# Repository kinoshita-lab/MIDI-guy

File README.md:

# MIDI Guy by Kinoshita Laboratory

[japanese version](./README.ja.md)

MIDI Guy is a sound module with SAM2695, a single chip General MIDI(GM) synthesizer.
It can generate GM's 127 sound programs such as "Acoustic Grand Piano", "Trumpet", etc.

You can also use effects and EQs. Please refer to the SAM2695's datasheet for details.
<https://www.dream.fr/pdf/Serie2000/SAM_Datasheets/SAM2695.pdf>

# Selling PCBA at tindie.com!
Please visit: <https://www.tindie.com/products/kinoshitalab/midi-guy-rev-21-kit/>

## What's new for Revision 2.1

- USB Power input is replaced from micro USB to USB Type-C
- PCB Dimension modification: fit for Frisk case
- Support both TRS MIDI type A and B
- Add UART In terminal for the convinience using with microcontroller

## Kit contents

- Pre-assembled circuit board
- 2 pcs. of 3.5mm TRS Jack
- 1 pc. of DIN <-> TRS(Type A) Conversion Cable

## What you will need

- USB C Cable
- Power source for USB, such as power adapter or PC
- MIDI cable
- MIDI Output Device e.g. MIDI Keyboard, PC with MIDI Interface

## How to assemble

Solder the included TRS Jacks to the places shown below.

## Usage

- Power: Connect the power source from USB
- MIDI In: Connect a MIDI message source(e.g. MIDI Keyboard, MIDI Interface connected to a PC)
- Audio Out: Outputs stereo sound, you can connect headphones directly.

## Schematics, design data, questions

<https://github.com/kinoshita-lab/MIDI-guy>

## Case Design
STL file made by @maks. Thank you!!
https://www.printables.com/model/1151667-case-for-a-midi-guy-pcb

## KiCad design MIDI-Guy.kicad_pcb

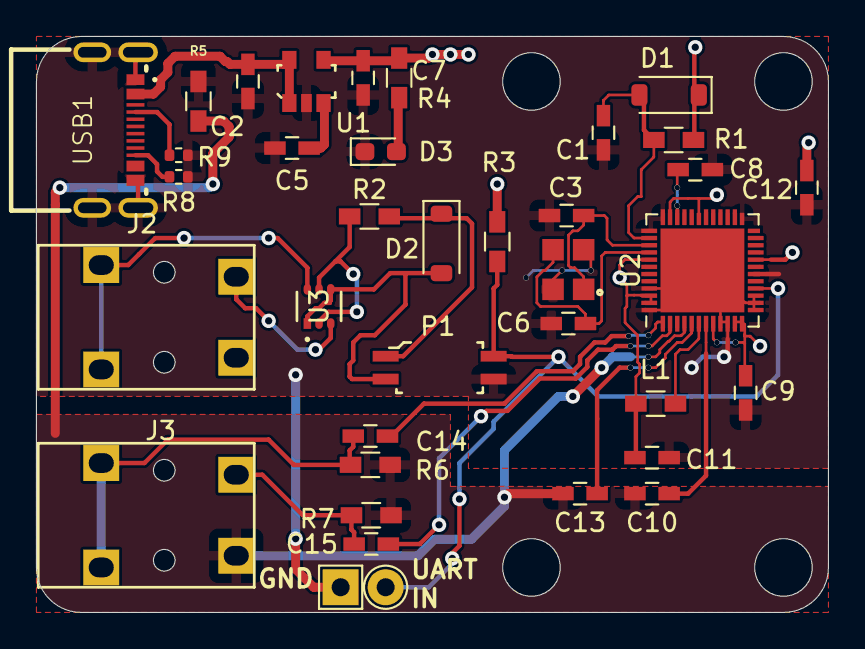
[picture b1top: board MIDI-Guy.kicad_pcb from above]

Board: 2 copper layers, 44.0 x 32.0 mm, 39 parts (0 on the bottom side), 25 nets.

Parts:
C1, C10: 1u; C_0603_HandSoldering
C2, C7, C14, C15: 10u; C_0603_HandSoldering
C3, C6: 10p; C_0603_HandSoldering
C5: 0.01u; C_0603_HandSoldering
C8: 4.7u; C_0603_HandSoldering
C9, C11, C12, C13: 0.1u; C_0603_HandSoldering
D1, D2: SM4007PL; D_SOD-123
D3: LED; LED_0603_1608Metric_Pad1.05x0.95mm_HandSolder
J2, J3: AudioJack3; 3.5mm_Stereo_TRS_PJ-3210-4A_and_ST-005-G
L1: GZ1608D222TF; L_0603_HandSoldering
P1: TLP291(GB-TP,SE; TLP291
R1: 10k; R_0603_HandSoldering
R2, R3: 220; R_0603_HandSoldering
R4: 1k; R_0603_HandSoldering
R5: 0; R_0603_HandSoldering
R6, R7: 47k; R_0603_HandSoldering
R8, R9: 5.1k; R_0402_1005Metric
REFe: MountingHole_3.2mm_M3_DIN965
REFe#2: MountingHole_3.2mm_M3_DIN965
TP1: TestPoint; TestPoint_THTPad_D2.0mm_Drill1.0mm
TP2: TestPoint; TestPoint_THTPad_2.0x2.0mm_Drill1.0mm
U1: TAR5S33; TAR5S33_Akizuki_Toshiba_SSOP5
U2: SAM2695; SAM2695_QFN-48-6x6mm_Pitch0.4mm
U3: BAS40DW-04-7-F; SOT-363_DIO
USB1: HRO TYPE-C-31-M-08A
Y1: TAXM12M4RDBCCT2T; OSCSC320X250X100N

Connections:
+3V3: C7.1, C9.1, C11.1, C12.1, D1.1 (K), L1.1, R1.1, R3.2, R4.1, U1.4 (Vout), U2.8 (VD33), U2.11 (VD33), U2.12 (WR/), U2.20 (VD33), U2.31 (VD33), U2.35 (VD33), U2.41 (VD33), U2.46 (VD33), U2.47 (XDIV)
A1: D2.2 (A), P1.2, U3.1 (A1), U3.4 (A2)
C1: R2.2, U3.2 (C1), U3.5 (C2)
GND: C1.2, C2.2, C3.2, C5.2, C6.2, C7.2, C8.2, C9.2, C11.2, C12.2, D3.1 (K), P1.3, R5.2, R8.1, R9.2, TP2.1, U1.2 (GND), U2.9 (GND), U2.10 (A0), U2.13 (GND), U2.14 (CS/), U2.15 (RD/), U2.18 (GND), U2.25 (GND), U2.36 (GND), U2.37 (TEST), U2.45 (GND), U2.48 (GND), U2.49 (die_pad), USB1.1 (GND), USB1.12 (GND), USB1.13 (SHIELD), Y1.2 (GND), Y1.4 (GND)
GNDA: C10.2, C13.1, J3.S, R5.1, R6.1, R7.1, U2.4 (AGND)
unnamed: C14.1, J3.T, R6.2
unnamed: C15.1, J3.R, R7.2
unnamed: C1.1, D1.2 (A), R1.2, U2.38 (RST/PD/)
unnamed: D2.1 (K), P1.1, R2.1
unnamed: D3.2 (A), R4.2
unnamed: C2.1, U1.1 (CONTROL), U1.5 (Vin), USB1.2 (VBUS)
unnamed: C5.1, U1.3 (NOISE)
unnamed: L1.2, U2.6 (VA33)
unnamed: P1.4, R3.1, TP1.1, U2.16 (MIDI_IN)
unnamed: C14.2, U2.1 (AOUTL)
unnamed: C15.2, U2.2 (AOUTR)
unnamed: C10.1, U2.7 (MICIN)
unnamed: C13.2, U2.5 (VCM)
unnamed: C8.1, U2.34 (OUTVC12)
unnamed: C3.1, U2.39 (X1), Y1.1
unnamed: C6.1, U2.40 (X2), Y1.3
unnamed: R9.1, USB1.4 (CC1)
unnamed: R8.2, USB1.10 (CC2)
in_R: J2.R, U3.3 (AC2)
in_T: J2.T, U3.6 (AC1)

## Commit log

2019-08-03 for MFT 2019
2019-08-03 add readme
2019-09-24 add manual in English
2019-09-24 add pdf manual(fit for A4 paper)
2019-10-04 add PCB Dimension info
2019-10-05 add dimension pdf
2020-02-08 move cap to avoid conflict on panellizing
2020-05-16 Create LICENSE
2021-05-19 - Change R3 value from 470 to 220, due to receiving failure according to the transfer current spec of TLP291 - Remove panelized pcb and gerber data, since they are not maintained
2024-06-21 Update to revision 2.1 with tidying unused, obsolete files
2024-07-16 add images how to assemble 2.1
2024-07-16 remove unused file
2024-07-16 add link to japanese
2024-07-17 replace wrong schematics
